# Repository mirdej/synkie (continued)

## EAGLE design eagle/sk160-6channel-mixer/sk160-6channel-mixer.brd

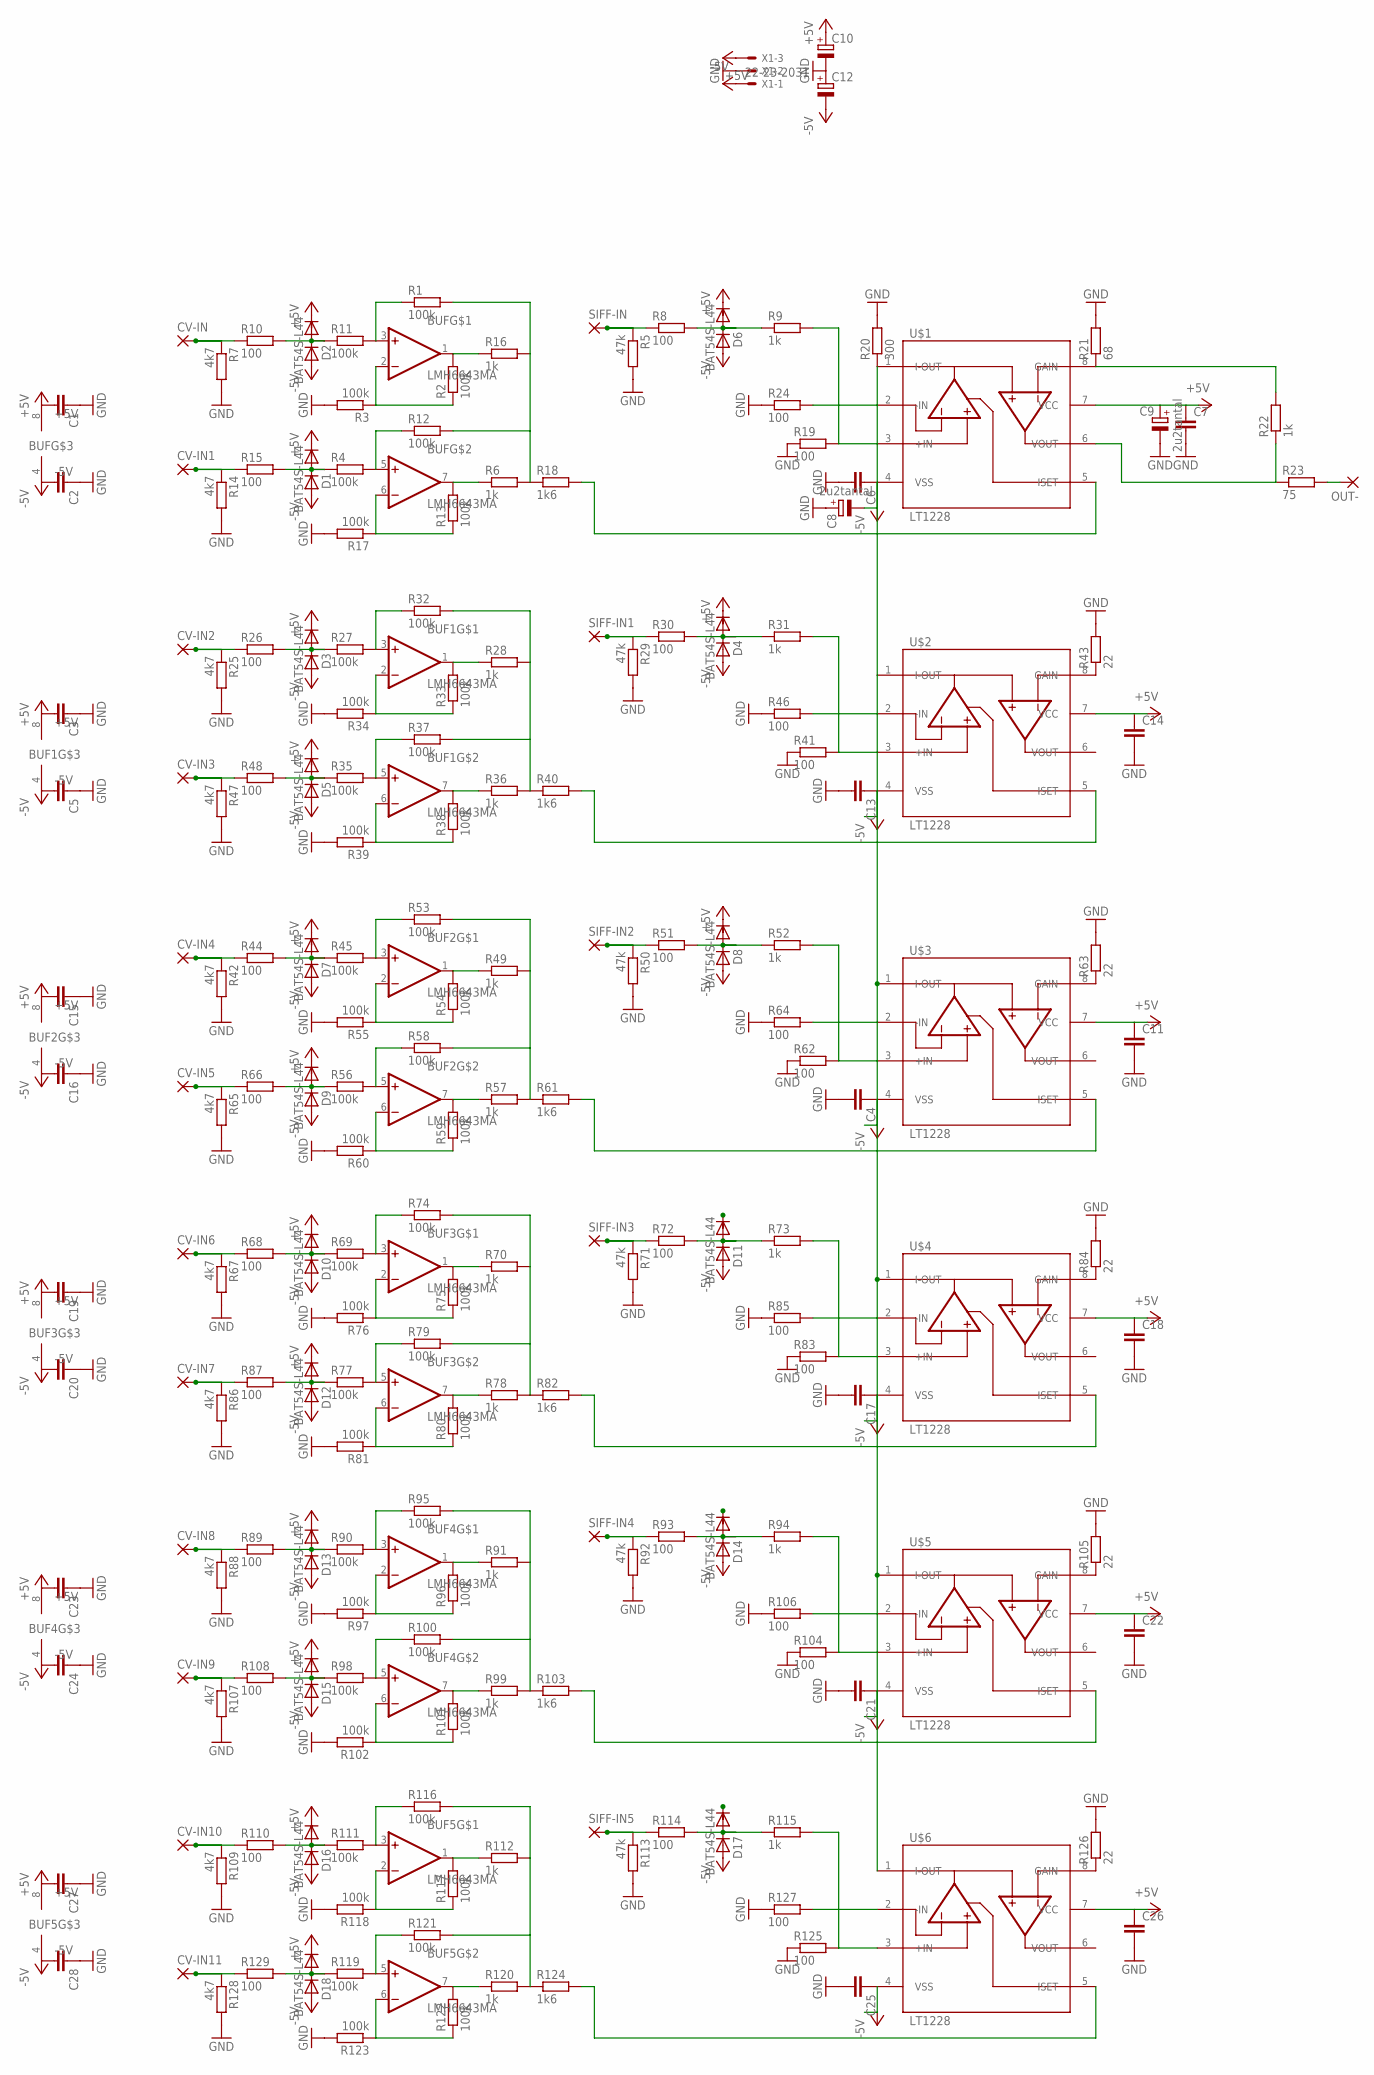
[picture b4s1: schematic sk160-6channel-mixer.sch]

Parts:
BUF, BUF1, BUF2, BUF3, BUF4, BUF5: LMH6643MA; SO08
C1, C2, C3, C4, C5, C6, C7, C11, C13, C14, C15, C16, C17, C18, C19, C20, C21, C22, C23, C24, C25, C26, C27, C28: C-EUC1206; C1206
C8, C9: 2u2tantal; CT6032
C10, C12: CPOL-EUCT6032; CT6032
CV-IN, CV-IN1, CV-IN2, CV-IN3, CV-IN4, CV-IN5, CV-IN6, CV-IN7, CV-IN8, CV-IN9, CV-IN10, CV-IN11: 3,17/1,1
D1, D2, D3, D4, D5, D6, D7, D8, D9, D10, D11, D12, D13, D14, D15, D16, D17, D18: BAT54S-L44; SOT23
OUT-: 3,17/1,1
R1, R2, R3, R4, R11, R12, R13, R17, R27, R32, R33, R34, R35, R37, R38, R39, R45, R53, R54, R55, R56, R58, R59, R60, R69, R74, R75, R76, R77, R79, R80, R81, R90, R95, R96, R97, R98, R100, R101, R102, R111, R116, R117, R118, R119, R121, R122, R123: 100k; R1206
R5, R29, R50, R71, R92, R113: 47k; R1206
R6, R9, R16, R22, R28, R31, R36, R49, R52, R57, R70, R73, R78, R91, R94, R99, R112, R115, R120: 1k; R1206
R7, R14, R25, R42, R47, R65, R67, R86, R88, R107, R109, R128: 4k7; R1206
R8, R10, R15, R19, R24, R26, R30, R41, R44, R46, R48, R51, R62, R64, R66, R68, R72, R83, R85, R87, R89, R93, R104, R106, R108, R110, R114, R125, R127, R129: 100; R1206
R18, R40, R61, R82, R103, R124: 1k6; R1206
R20: 300; R1206
R21: 68; R1206
R23: 75; R1206
R43, R63, R84, R105, R126: 22; R1206
SIFF-IN, SIFF-IN1, SIFF-IN2, SIFF-IN3, SIFF-IN4, SIFF-IN5: 3,17/1,1
U$1, U$2, U$3, U$4, U$5, U$6: LT1228; SO08
X1: 22-23-2031

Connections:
+5V: BUF.8 (+5V), BUF1.8 (+5V), BUF2.8 (+5V), BUF3.8 (+5V), BUF4.8 (+5V), BUF5.8 (+5V), C1.2, C3.2, C7.1, C9.+, C10.+, C11.1, C14.1, C15.2, C18.1, C19.2, C22.1, C23.2, C26.1, C27.2, D1.2 (C), D2.2 (C), D3.2 (C), D4.2 (C), D5.2 (C), D6.2 (C), D7.2 (C), D8.2 (C), D9.2 (C), D10.2 (C), D11.2 (C), D12.2 (C), D13.2 (C), D14.2 (C), D15.2 (C), D16.2 (C), D17.2 (C), D18.2 (C), U$1.7 (VCC), U$2.7 (VCC), U$3.7 (VCC), U$4.7 (VCC), U$5.7 (VCC), U$6.7 (VCC), X1.3
-5V: BUF.4 (-5V), BUF1.4 (-5V), BUF2.4 (-5V), BUF3.4 (-5V), BUF4.4 (-5V), BUF5.4 (-5V), C2.2, C4.1, C5.2, C6.1, C8.-, C12.-, C13.1, C16.2, C17.1, C20.2, C21.1, C24.2, C25.1, C28.2, D1.1 (A), D2.1 (A), D3.1 (A), D4.1 (A), D5.1 (A), D6.1 (A), D7.1 (A), D8.1 (A), D9.1 (A), D10.1 (A), D11.1 (A), D12.1 (A), D13.1 (A), D14.1 (A), D15.1 (A), D16.1 (A), D17.1 (A), D18.1 (A), U$1.4 (VSS), U$2.4 (VSS), U$3.4 (VSS), U$4.4 (VSS), U$5.4 (VSS), U$6.4 (VSS), X1.1
GND: C1.1, C2.1, C3.1, C4.2, C5.1, C6.2, C7.2, C8.+, C9.-, C10.-, C11.2, C12.+, C13.2, C14.2, C15.1, C16.1, C17.2, C18.2, C19.1, C20.1, C21.2, C22.2, C23.1, C24.1, C25.2, C26.2, C27.1, C28.1, R3.2, R5.2, R7.2, R14.2, R17.2, R19.1, R20.2, R21.2, R24.1, R25.2, R29.2, R34.2, R39.2, R41.1, R42.2, R43.2, R46.1, R47.2, R50.2, R55.2, R60.2, R62.1, R63.2, R64.1, R65.2, R67.2, R71.2, R76.2, R81.2, R83.1, R84.2, R85.1, R86.2, R88.2, R92.2, R97.2, R102.2, R104.1, R105.2, R106.1, R107.2, R109.2, R113.2, R118.2, R123.2, R125.1, R126.2, R127.1, R128.2, X1.2
unnamed: CV-IN1.1, R14.1, R15.1
unnamed: D1.3 (AC), R4.1, R15.2
unnamed: CV-IN2.1, R25.1, R26.1
unnamed: BUF.2 (-IN), R2.1, R3.1
unnamed: R9.2, R19.2, U$1.3 (+IN)
unnamed: CV-IN4.1, R42.1, R44.1
unnamed: BUF.5 (+IN), R4.2, R12.1
unnamed: BUF.7 (OUT), R6.1, R13.2
unnamed: R21.1, R22.2, U$1.8 (GAIN)
unnamed: CV-IN.1, R7.1, R10.1
unnamed: D2.3 (AC), R10.2, R11.1
unnamed: BUF.6 (-IN), R13.1, R17.1
unnamed: D3.3 (AC), R26.2, R27.1
unnamed: BUF.3 (+IN), R1.1, R11.2
unnamed: R5.1, R8.1, SIFF-IN.1
unnamed: D6.3 (AC), R8.2, R9.1
unnamed: BUF.1 (OUT), R2.2, R16.1
unnamed: R18.2, U$1.5 (ISET)
unnamed: R1.2, R6.2, R12.2, R16.2, R18.1
unnamed: R22.1, R23.1, U$1.6 (VOUT)
unnamed: OUT-.1, R23.2
unnamed: R24.2, U$1.2 (-IN)
unnamed: BUF1.3 (+IN), R27.2, R32.1
unnamed: BUF1.1 (OUT), R28.1, R33.2
unnamed: R28.2, R32.2, R36.2, R37.2, R40.1
unnamed: R29.1, R30.1, SIFF-IN1.1
unnamed: D4.3 (AC), R30.2, R31.1
unnamed: R31.2, R41.2, U$2.3 (+IN)
unnamed: BUF1.2 (-IN), R33.1, R34.1
unnamed: BUF1.5 (+IN), R35.2, R37.1
unnamed: BUF1.7 (OUT), R36.1, R38.2
unnamed: BUF1.6 (-IN), R38.1, R39.1
unnamed: R40.2, U$2.5 (ISET)
unnamed: R20.1, U$1.1 (I-OUT), U$2.1 (I-OUT), U$3.1 (I-OUT), U$4.1 (I-OUT), U$5.1 (I-OUT), U$6.1 (I-OUT)
unnamed: D7.3 (AC), R44.2, R45.1
unnamed: BUF2.3 (+IN), R45.2, R53.1
unnamed: BUF2.1 (OUT), R49.1, R54.2
unnamed: R46.2, U$2.2 (-IN)
unnamed: CV-IN3.1, R47.1, R48.1
unnamed: D5.3 (AC), R35.1, R48.2
unnamed: R49.2, R53.2, R57.2, R58.2, R61.1
unnamed: R43.1, U$2.8 (GAIN)
unnamed: R50.1, R51.1, SIFF-IN2.1
unnamed: D8.3 (AC), R51.2, R52.1
unnamed: R52.2, R62.2, U$3.3 (+IN)
unnamed: BUF2.2 (-IN), R54.1, R55.1
unnamed: BUF2.5 (+IN), R56.2, R58.1
unnamed: BUF2.7 (OUT), R57.1, R59.2
unnamed: BUF2.6 (-IN), R59.1, R60.1
unnamed: R61.2, U$3.5 (ISET)
unnamed: R64.2, U$3.2 (-IN)
unnamed: CV-IN5.1, R65.1, R66.1
unnamed: D9.3 (AC), R56.1, R66.2
unnamed: R63.1, U$3.8 (GAIN)
unnamed: CV-IN6.1, R67.1, R68.1
unnamed: D10.3 (AC), R68.2, R69.1
unnamed: BUF3.3 (+IN), R69.2, R74.1
unnamed: BUF3.1 (OUT), R70.1, R75.2
unnamed: R70.2, R74.2, R78.2, R79.2, R82.1
unnamed: R71.1, R72.1, SIFF-IN3.1
unnamed: D11.3 (AC), R72.2, R73.1
unnamed: R73.2, R83.2, U$4.3 (+IN)
unnamed: BUF3.2 (-IN), R75.1, R76.1
unnamed: BUF3.5 (+IN), R77.2, R79.1
unnamed: BUF3.7 (OUT), R78.1, R80.2
unnamed: BUF3.6 (-IN), R80.1, R81.1
unnamed: R82.2, U$4.5 (ISET)
unnamed: R85.2, U$4.2 (-IN)
unnamed: CV-IN7.1, R86.1, R87.1
unnamed: D12.3 (AC), R77.1, R87.2
unnamed: R84.1, U$4.8 (GAIN)
unnamed: CV-IN8.1, R88.1, R89.1
unnamed: D13.3 (AC), R89.2, R90.1
unnamed: BUF4.3 (+IN), R90.2, R95.1
unnamed: BUF4.1 (OUT), R91.1, R96.2
unnamed: R91.2, R95.2, R99.2, R100.2, R103.1
unnamed: R92.1, R93.1, SIFF-IN4.1
unnamed: D14.3 (AC), R93.2, R94.1
unnamed: R94.2, R104.2, U$5.3 (+IN)
unnamed: BUF4.2 (-IN), R96.1, R97.1
unnamed: BUF4.5 (+IN), R98.2, R100.1
unnamed: BUF4.7 (OUT), R99.1, R101.2
unnamed: BUF4.6 (-IN), R101.1, R102.1
unnamed: R103.2, U$5.5 (ISET)
unnamed: R106.2, U$5.2 (-IN)
unnamed: CV-IN9.1, R107.1, R108.1
unnamed: D15.3 (AC), R98.1, R108.2
unnamed: R105.1, U$5.8 (GAIN)
unnamed: CV-IN10.1, R109.1, R110.1
unnamed: D16.3 (AC), R110.2, R111.1
unnamed: BUF5.3 (+IN), R111.2, R116.1
unnamed: BUF5.1 (OUT), R112.1, R117.2
unnamed: R112.2, R116.2, R120.2, R121.2, R124.1
unnamed: R113.1, R114.1, SIFF-IN5.1
unnamed: D17.3 (AC), R114.2, R115.1
unnamed: R115.2, R125.2, U$6.3 (+IN)
unnamed: BUF5.2 (-IN), R117.1, R118.1
unnamed: BUF5.5 (+IN), R119.2, R121.1
unnamed: BUF5.7 (OUT), R120.1, R122.2
unnamed: BUF5.6 (-IN), R122.1, R123.1
unnamed: R124.2, U$6.5 (ISET)
unnamed: R127.2, U$6.2 (-IN)
unnamed: CV-IN11.1, R128.1, R129.1
unnamed: D18.3 (AC), R119.1, R129.2
unnamed: R126.1, U$6.8 (GAIN)

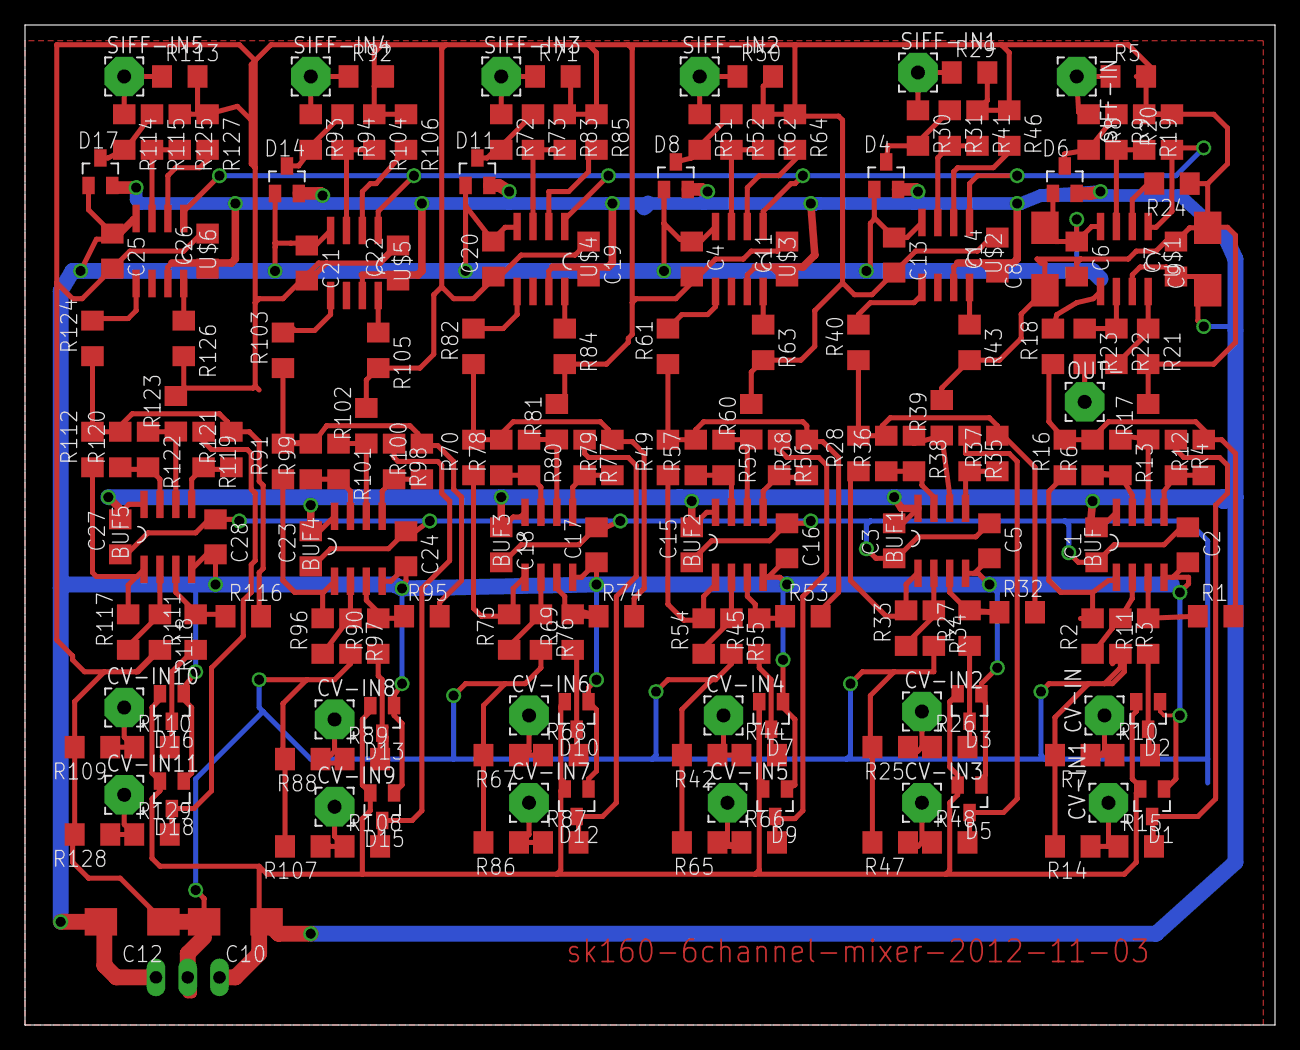
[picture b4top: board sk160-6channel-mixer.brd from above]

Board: 2 copper layers, 100.0 x 80.0 mm, 207 parts (1 on the bottom side), 108 nets.

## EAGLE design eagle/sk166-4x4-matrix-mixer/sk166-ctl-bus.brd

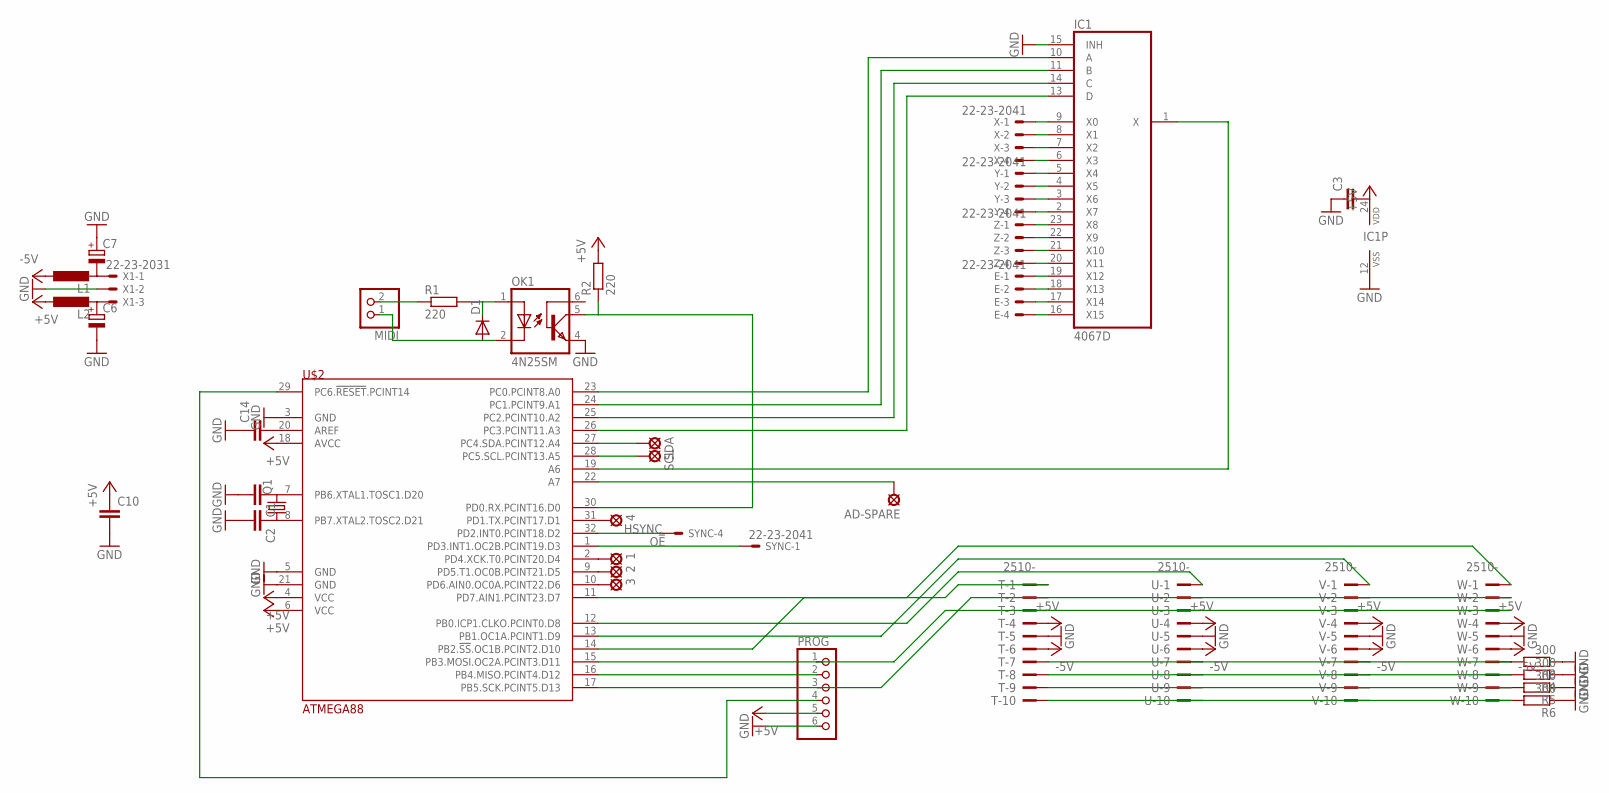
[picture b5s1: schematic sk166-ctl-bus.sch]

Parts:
1, 2, 3, 4: LSP11
AD-SPARE: LSP11
C1, C2: C-EUC1206; C1206
C3, C10, C14: C-EUC0603; C0603
C6, C7: CPOL-EUCT3528; CT3528
D1: DIODE-MINIMELF; MINIMELF
E: 22-23-2041
IC1: 4067D; SO24W
L1, L2: L-EUL2012C; L2012C
MIDI: PINHD-1X2; 1X02
OK1: 4N25SM; DIL6-SMD
PROG: PINHD-1X6; 1X06
Q1: CRYSTALHC49UP; HC49UP
R1, R2: 220; R1206
R3, R4, R5, R6: 300; R1206
SCL: LSP11
SDA: LSP11
SYNC: 22-23-2041
T: 2510-; PAK100/2500-10
U: 2510-; PAK100/2500-10
U$2: ATMEGA88; TQFP32-08
V: 2510-; PAK100/2500-10
W: 2510-; PAK100/2500-10
X: 22-23-2041
X1: 22-23-2031
Y: 22-23-2041
Z: 22-23-2041

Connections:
+5V: C3.2, C10.1, IC1.24 (VDD), L2.1, PROG.5, R2.2, T.4, U.4, U$2.4 (VCC), U$2.6 (VCC), U$2.18 (AVCC), V.4, W.4
-5V: L1.1, T.6, U.6, V.6, W.6
CST: T.1, U$2.11 (PD7.AIN1.PCINT23.D7)
CSU: U.1, U$2.12 (PB0.ICP1.CLKO.PCINT0.D8)
CSV: U$2.13 (PB1.OC1A.PCINT1.D9), V.1
CSW: U$2.14 (PB2.!SS!.OC1B.PCINT2.D10), W.1
GND: C1.2, C2.2, C3.1, C6.-, C7.+, C10.2, C14.1, IC1.12 (VSS), IC1.15 (INH), OK1.4 (EMI), PROG.6, R3.1, R4.1, R5.1, R6.1, T.5, U.5, U$2.3 (GND), U$2.5 (GND), U$2.21 (GND), V.5, W.5, X1.2
HSYNC: SYNC.4, U$2.32 (PD2.INT0.PCINT18.D2)
MIDI: OK1.5 (COL), R2.1, U$2.30 (PD0.RX.PCINT16.D0)
MISO: PROG.2, U$2.16 (PB4.MISO.PCINT4.D12)
MOSI: PROG.1, T.3, U.3, U$2.15 (PB3.MOSI.OC2A.PCINT3.D11), V.3, W.3
unnamed: PROG.4, U$2.29 (PC6.!RESET!.PCINT14)
unnamed: R3.2, T.7, U.7, V.7, W.7
unnamed: C1.1, Q1.2, U$2.7 (PB6.XTAL1.TOSC1.D20)
unnamed: C2.1, Q1.1, U$2.8 (PB7.XTAL2.TOSC2.D21)
unnamed: IC1.1 (X), U$2.19 (A6)
unnamed: IC1.10 (A), U$2.23 (PC0.PCINT8.A0)
unnamed: R4.2, T.8, U.8, V.8, W.8
unnamed: R5.2, T.9, U.9, V.9, W.9
unnamed: R6.2, T.10, U.10, V.10, W.10
unnamed: IC1.11 (B), U$2.24 (PC1.PCINT9.A1)
unnamed: IC1.14 (C), U$2.25 (PC2.PCINT10.A2)
unnamed: IC1.13 (D), U$2.26 (PC3.PCINT11.A3)
unnamed: AD-SPARE.MP, U$2.22 (A7)
unnamed: IC1.8 (X1), X.2
unnamed: IC1.7 (X2), X.3
unnamed: 1.MP, U$2.2 (PD4.XCK.T0.PCINT20.D4)
unnamed: MIDI.2, R1.1
unnamed: D1.A, MIDI.1, OK1.2 (C)
unnamed: D1.C, OK1.1 (A), R1.2
unnamed: 2.MP, U$2.9 (PD5.T1.OC0B.PCINT21.D5)
unnamed: 3.MP, U$2.10 (PD6.AIN0.OC0A.PCINT22.D6)
unnamed: 4.MP, U$2.31 (PD1.TX.PCINT17.D1)
unnamed: IC1.4 (X5), Y.2
unnamed: IC1.3 (X6), Y.3
unnamed: IC1.2 (X7), Y.4
unnamed: IC1.22 (X9), Z.2
unnamed: IC1.21 (X10), Z.3
unnamed: IC1.20 (X11), Z.4
unnamed: C7.-, L1.2, X1.1
unnamed: C6.+, L2.2, X1.3
unnamed: E.2, IC1.18 (X13)
unnamed: C14.2, U$2.20 (AREF)
unnamed: E.3, IC1.17 (X14)
unnamed: SDA.MP, U$2.27 (PC4.SDA.PCINT12.A4)
unnamed: SCL.MP, U$2.28 (PC5.SCL.PCINT13.A5)
unnamed: E.4, IC1.16 (X15)
O!E: SYNC.1, U$2.1 (PD3.INT1.OC2B.PCINT19.D3)
SCK: PROG.3, T.2, U.2, U$2.17 (PB5.SCK.PCINT5.D13), V.2, W.2
XT: IC1.9 (X0), X.1
YT: IC1.5 (X4), Y.1
YU: IC1.6 (X3), X.4
ZT: IC1.23 (X8), Z.1
ZZT: E.1, IC1.19 (X12)

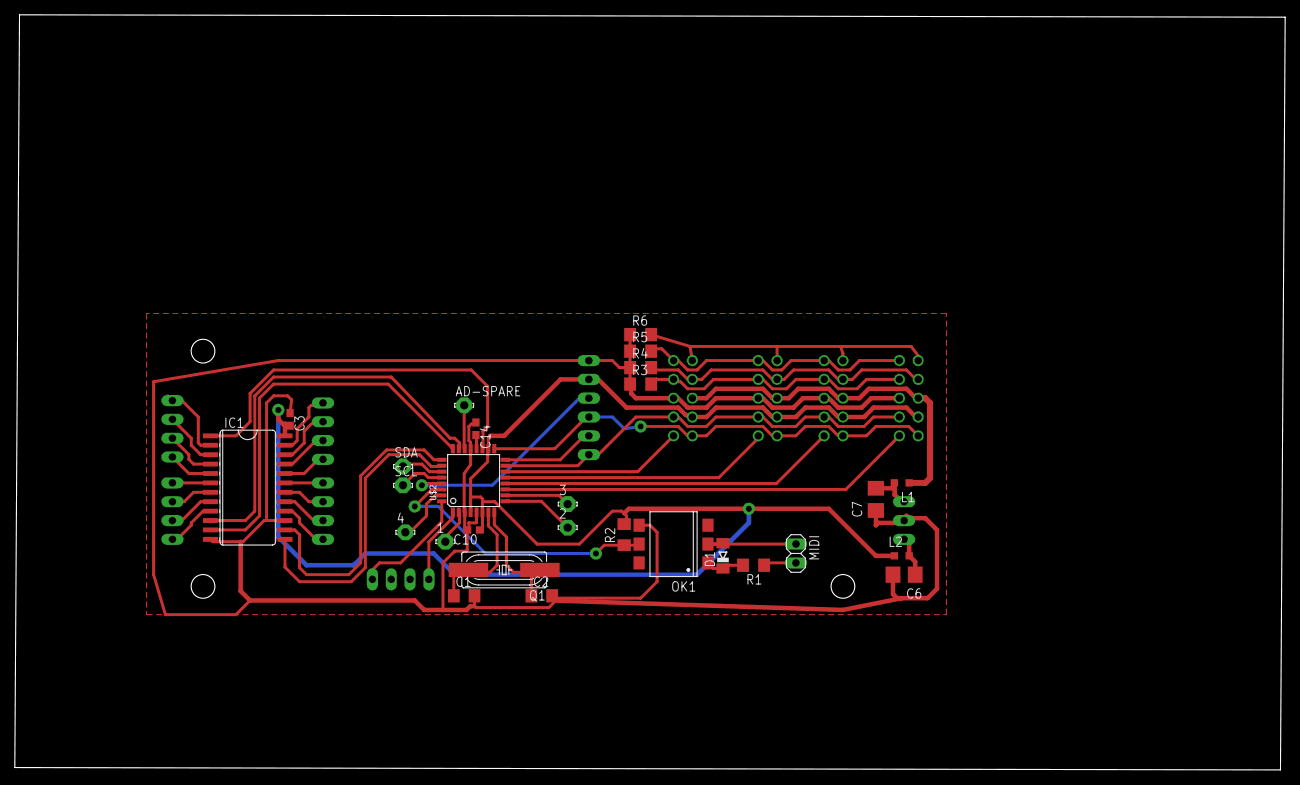
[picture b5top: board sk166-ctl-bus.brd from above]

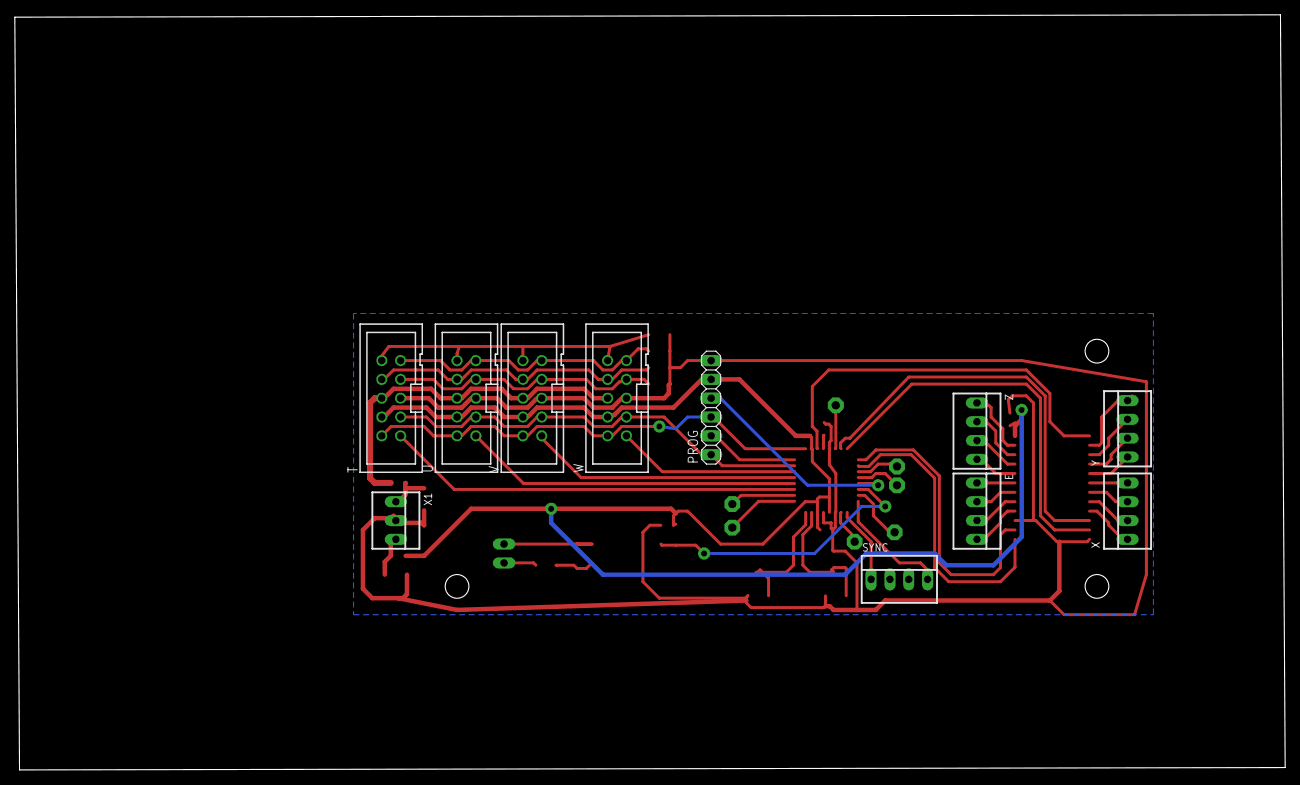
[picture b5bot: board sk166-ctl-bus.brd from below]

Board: 2 copper layers, 171.4 x 101.9 mm, 39 parts (11 on the bottom side), 54 nets.

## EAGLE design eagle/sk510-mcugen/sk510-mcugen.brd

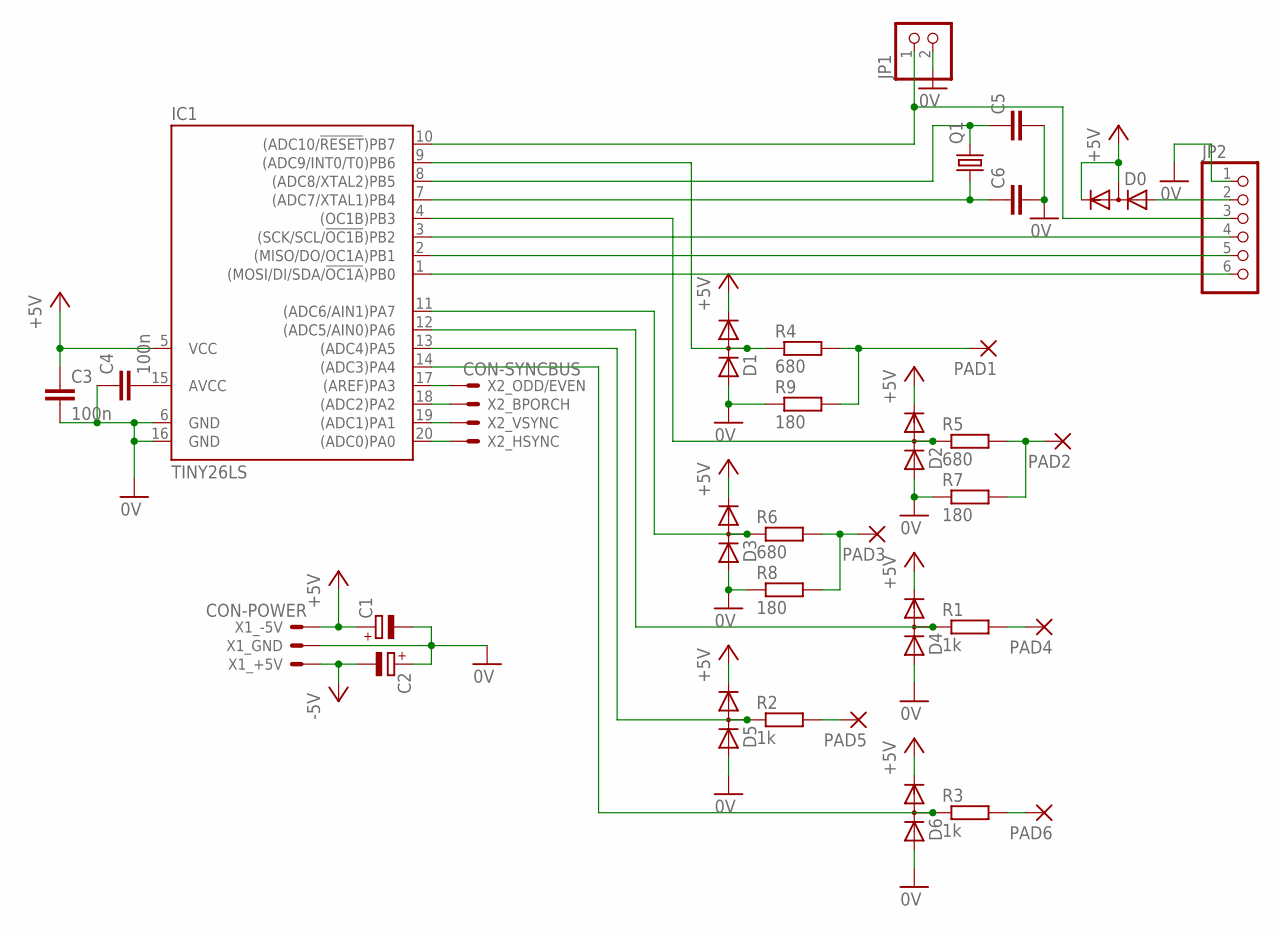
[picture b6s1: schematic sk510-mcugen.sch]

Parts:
C1, C2: CPOL-EUCT3528; CT3528
C3, C4: 100n; C0805
C5, C6: C-EUC0805; C0805
D0, D1, D2, D3, D4, D5, D6: DIODE_2CACA-SOT23; SOT23
IC1: TINY26LS; SO20L
JP1: PINHD-1X2; 1X02
JP2: PINHD-1X6; 1X06
PAD1, PAD2, PAD3, PAD4, PAD5, PAD6: 3,17/1,1
Q1: CRYSTALHC49UP; HC49UP
R1, R2, R3: 1k; R0805
R4, R5, R6: 680; R0805
R7, R8, R9: 180; R0805
X1: CON-POWER; 22-23-2031
X2: CON-SYNCBUS; 22-23-2041

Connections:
0V: C1.-, C2.+, C3.2, C4.1, C5.2, C6.2, D1.1 (A), D2.1 (A), D3.1 (A), D4.1 (A), D5.1 (A), D6.1 (A), IC1.6 (GND), IC1.16 (GND), JP1.2, JP2.1, R7.1, R8.1, R9.1, X1.2
+5V: C1.+, C3.1, D0.2 (C), D0.3 (AC), D1.2 (C), D2.2 (C), D3.2 (C), D4.2 (C), D5.2 (C), D6.2 (C), IC1.5 (VCC), X1.1
-5V: C2.-, X1.3
unnamed: C4.2, IC1.15 (AVCC)
unnamed: C5.1, IC1.8 ((ADC8/XTAL2)PB5), Q1.2
unnamed: C6.1, IC1.7 ((ADC7/XTAL1)PB4), Q1.1
unnamed: D0.1 (A), JP2.2
unnamed: IC1.10 ((ADC10/!RESET!)PB7), JP1.1, JP2.3
unnamed: IC1.3 ((SCK/SCL/!OC1B!)PB2), JP2.4
unnamed: IC1.2 ((MISO/DO/OC1A)PB1), JP2.5
unnamed: IC1.1 ((MOSI/DI/SDA/!OC1A!)PB0), JP2.6
unnamed: D1.3 (AC), IC1.9 ((ADC9/INT0/T0)PB6), R4.1
unnamed: IC1.20 ((ADC0)PA0), X2.4
unnamed: IC1.19 ((ADC1)PA1), X2.3
unnamed: IC1.18 ((ADC2)PA2), X2.2
unnamed: IC1.17 ((AREF)PA3), X2.1
unnamed: D2.3 (AC), IC1.4 ((OC1B)PB3), R5.1
unnamed: PAD4.1, R1.2
unnamed: D3.3 (AC), IC1.11 ((ADC6/AIN1)PA7), R6.1
unnamed: PAD5.1, R2.2
unnamed: PAD6.1, R3.2
unnamed: D4.3 (AC), IC1.12 ((ADC5/AIN0)PA6), R1.1
unnamed: PAD1.1, R4.2, R9.2
unnamed: D5.3 (AC), IC1.13 ((ADC4)PA5), R2.1
unnamed: PAD2.1, R5.2, R7.2
unnamed: D6.3 (AC), IC1.14 ((ADC3)PA4), R3.1
unnamed: PAD3.1, R6.2, R8.2

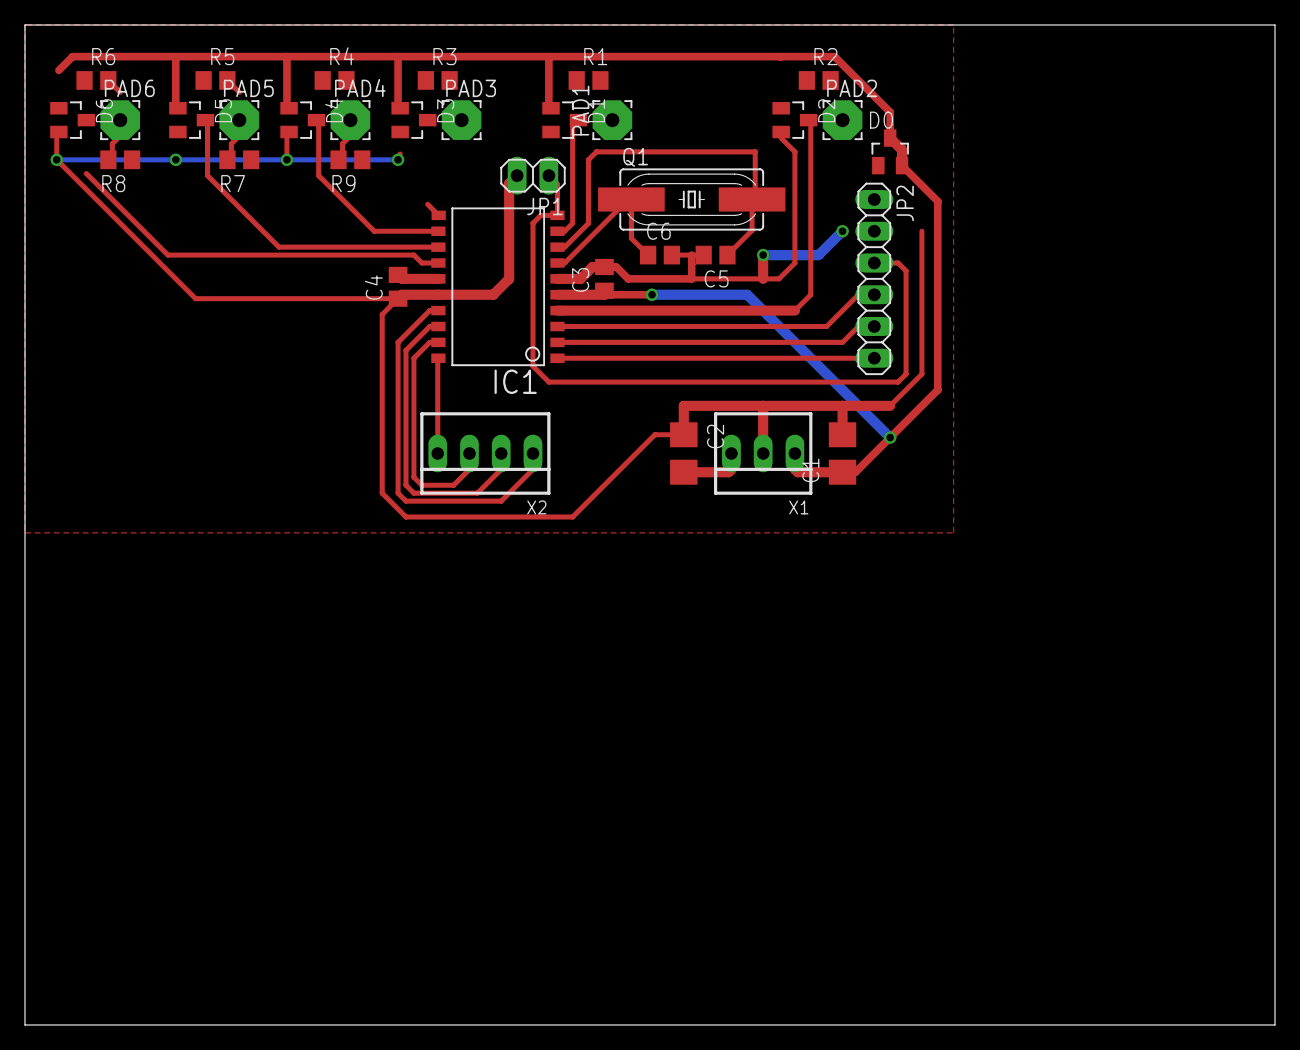
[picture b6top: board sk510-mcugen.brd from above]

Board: 2 copper layers, 100.0 x 80.0 mm, 34 parts (0 on the bottom side), 27 nets.

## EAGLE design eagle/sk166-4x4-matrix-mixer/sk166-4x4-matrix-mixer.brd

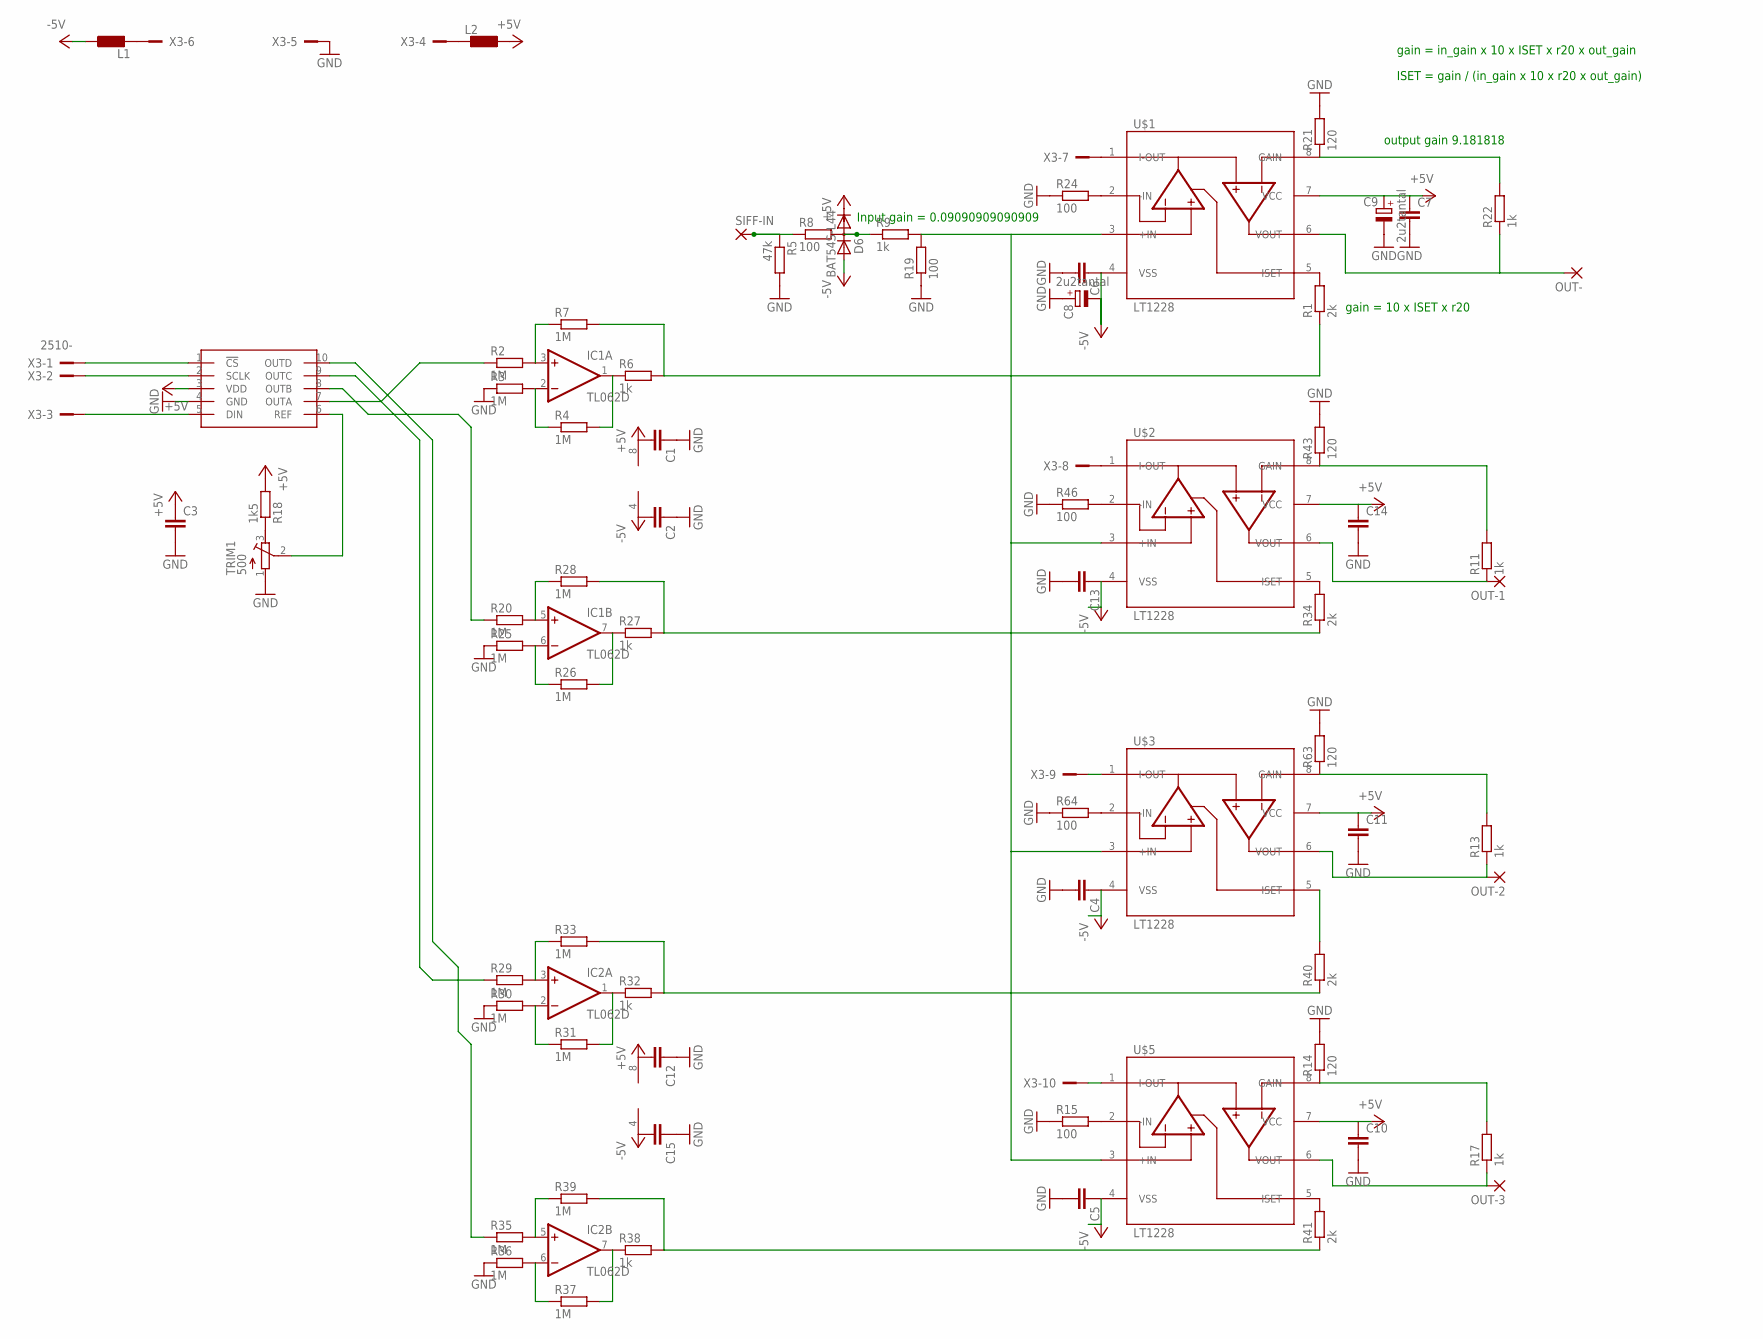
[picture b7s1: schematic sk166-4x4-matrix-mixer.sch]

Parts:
C1, C2, C3, C4, C5, C6, C7, C10, C11, C12, C13, C14, C15: C-EUC1206; C1206
C8, C9: 2u2tantal; CT6032
D6: BAT54S-L44; SOT23
IC1, IC2: TL062D; SO08
L1, L2: LL2012C; L2012C
OUT-, OUT-1, OUT-2, OUT-3: 3,17/1,1
R1, R34, R40, R41: 2k; R1206
R2, R3, R4, R7, R20, R25, R26, R28, R29, R30, R31, R33, R35, R36, R37, R39: 1M; R1206
R5: 47k; R1206
R6, R9, R11, R13, R17, R22, R27, R32, R38: 1k; R1206
R8, R15, R19, R24, R46, R64: 100; R1206
R14, R21, R43, R63: 120; R1206
R18: 1k5; R1206
SIFF-IN: 3,17/1,1
TRIM1: 500; RTRIM64Y
U$1, U$2, U$3, U$5: LT1228; SO08
U$4: MAX5741; UMAX10
X3: 2510-; PAK100/2500-10

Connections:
!CS: U$4.1 (!CS), X3.1
+5V: C1.2, C3.1, C7.1, C9.+, C10.1, C11.1, C12.2, C14.1, D6.2 (C), IC1.8 (V+), IC2.8 (V+), L2.1, R18.2, U$1.7 (VCC), U$2.7 (VCC), U$3.7 (VCC), U$4.3 (VDD), U$5.7 (VCC)
-5V: C2.2, C4.1, C5.1, C6.1, C8.-, C13.1, C15.2, D6.1 (A), IC1.4 (V-), IC2.4 (V-), L1.1, U$1.4 (VSS), U$2.4 (VSS), U$3.4 (VSS), U$5.4 (VSS)
DATA: U$4.5 (DIN), X3.3
GND: C1.1, C2.1, C3.2, C4.2, C5.2, C6.2, C7.2, C8.+, C9.-, C10.2, C11.2, C12.1, C13.2, C14.2, C15.1, R3.1, R5.2, R14.2, R15.1, R19.1, R21.2, R24.1, R25.1, R30.1, R36.1, R43.2, R46.1, R63.2, R64.1, TRIM1.1 (E), U$4.4 (GND), X3.5
unnamed: U$5.1 (I-OUT), X3.10
unnamed: OUT-1.1, R11.1, U$2.6 (VOUT)
unnamed: OUT-2.1, R13.1, U$3.6 (VOUT)
unnamed: L2.2, X3.4
unnamed: L1.2, X3.6
unnamed: U$1.1 (I-OUT), X3.7
unnamed: IC1.3 (+IN), R2.2, R7.1
unnamed: IC1.2 (-IN), R3.2, R4.1
unnamed: R21.1, R22.2, U$1.8 (GAIN)
unnamed: IC1.1 (OUT), R4.2, R6.1
unnamed: R1.1, R6.2, R7.2
unnamed: R1.2, U$1.5 (ISET)
unnamed: R2.1, U$4.7 (OUTA)
unnamed: R5.1, R8.1, SIFF-IN.1
unnamed: D6.3 (AC), R8.2, R9.1
unnamed: U$2.1 (I-OUT), X3.8
unnamed: R9.2, R19.2, U$1.3 (+IN), U$2.3 (+IN), U$3.3 (+IN), U$5.3 (+IN)
unnamed: OUT-.1, R22.1, U$1.6 (VOUT)
unnamed: R24.2, U$1.2 (-IN)
unnamed: R18.1, TRIM1.3 (A)
unnamed: R41.2, U$5.5 (ISET)
unnamed: R15.2, U$5.2 (-IN)
unnamed: R14.1, R17.2, U$5.8 (GAIN)
unnamed: OUT-3.1, R17.1, U$5.6 (VOUT)
unnamed: R20.1, U$4.8 (OUTB)
unnamed: TRIM1.2 (S), U$4.6 (REF)
unnamed: IC1.5 (+IN), R20.2, R28.1
unnamed: IC1.6 (-IN), R25.2, R26.1
unnamed: R34.2, U$2.5 (ISET)
unnamed: U$3.1 (I-OUT), X3.9
unnamed: IC1.7 (OUT), R26.2, R27.1
unnamed: R27.2, R28.2, R34.1
unnamed: IC2.3 (+IN), R29.2, R33.1
unnamed: R46.2, U$2.2 (-IN)
unnamed: IC2.2 (-IN), R30.2, R31.1
unnamed: IC2.1 (OUT), R31.2, R32.1
unnamed: R32.2, R33.2, R40.1
unnamed: R11.2, R43.1, U$2.8 (GAIN)
unnamed: IC2.5 (+IN), R35.2, R39.1
unnamed: IC2.6 (-IN), R36.2, R37.1
unnamed: IC2.7 (OUT), R37.2, R38.1
unnamed: R38.2, R39.2, R41.1
unnamed: R35.1, U$4.10 (OUTD)
unnamed: R29.1, U$4.9 (OUTC)
unnamed: R40.2, U$3.5 (ISET)
unnamed: R64.2, U$3.2 (-IN)
unnamed: R13.2, R63.1, U$3.8 (GAIN)
SCK: U$4.2 (SCLK), X3.2

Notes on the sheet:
Input gain = 0.09090909090909
output gain 9.181818
gain = 10 x ISET x r20
gain = in_gain x 10 x ISET x r20 x out_gain
ISET = gain / (in_gain x 10 x r20 x out_gain)
